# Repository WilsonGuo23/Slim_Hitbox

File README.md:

# Slim Hitbox Enclosure

This repository contains 3D models, assembly instructions, and detailed documentation for building a compact, 3D-printed hitbox-style arcade controller.

## Project Overview

This Slim Hitbox Enclosure provides a slim, portable alternative to traditional arcade controllers, making it ideal for travel and easy setup. It supports 3D printing, simple assembly, and an ergonomic design. 

> **Note**: Version 1 is exclusively in the southpaw (left-handed) layout. Currently, there is no orthodox (right-handed) version.

## Features

- **Compact and Slim Design**: A low-profile layout optimized for easy handling and storage.
- **3D Printable Components**: Fully printable in standard PLA/ABS materials.
- **Ergonomic Design**: Includes a wrist rest for comfort.
- **Comfortable Assembly**: Chamfered screw holes provide a smoother finish.

## Attributions

This project uses GP2040 to enable the microcontroller to function as a game controller. Special thanks to the knowledgeable members of the GP2040 Discord community for their assistance and expertise, and to the helpful contributors on the r/pcb subreddit for reviewing the board's usability before it was sent for production.

## Prerequisites

- Access to a 3D printer and filament (PLA, ABS, or similar recommended)
- Personal Computer with USB port
- Soldering equipment and basic assembly tools

## Instructions

1. **PCB Manufacturing**: Have the PCB manufactured using the Gerber files in the `fab` folder.
2. **Download STL Files**: Access the STL files from the `models` directory.
3. **Slice and Print**: Use slicing software like Cura or PrusaSlicer to prepare and print the models. Adjust settings as needed based on your specific printer and filament.
4. **Assemble**: Follow the assembly instructions below.

## Parts List

- **Buttons**: 9x 30mm buttons, 3x 24mm buttons
- **Keycaps**: 5x keycaps
- **Panels**: 1x top panel, 1x bottom panel
- **Cables**: 1x Micro USB male to USB male cable ([link](https://www.amazon.com/gp/product/B08BZD66H4/ref=ppx_yo_dt_b_search_asin_title?ie=UTF8&psc=1)) 1x, 1x USB female to USB male cable
  1. (length should match your preferred distance to console or PC)
- **Hardware**: 6x M3 x 20mm screws, 6x M3 bolts
- **Feet**: 6x printed feet
  1. (ensure bolts fit snugly)
- **Electrical Components**:
  - 1x Raspberry Pi Pico
  - 17x MX Cherry or MX Cherry-compatible keyswitches
  - 2 rows of 100-pin male header pins ([link](https://www.amazon.com/dp/B06ZZN8L9S?ref=ppx_yo2ov_dt_b_fed_asin_title))
  - 1x PCB

## Assembly Instructions

1. **Prepare Feet**: Apply a strong bonding agent to the inner walls of each foot, then insert bolts into all six printed feet.
2. **Microcontroller Setup**: Solder male header pins to the Pico microcontroller.
3. **PCB Assembly**: Solder the microcontroller to the PCB using the header pins.
4. **Keyswitch Installation**: Solder all 17 keyswitches onto the PCB.
5. **Cable Guide**: Attach the Micro USB to USB cable to the Pico and guide it through the channels in the top panel.
6. **Enclosure Assembly**: Place the PCB between the top and bottom panels.
7. **Secure Panels**: Screw the panels together and attach them with the feet.
8. **Install Buttons**: Attach all printed buttons, following the image shown below.

9. **Attach USB Cable**: Connect the USB female-to-male cable to the exposed USB head.

## Configuration

1. **Download Firmware**: Get the appropriate microcontroller `.uf2` file from the [GP2040 website](https://gp2040-ce.info/downloads/).
2. **Connect and Install Firmware**: Plug the USB cable into a PC, then drag the `.uf2` file into the storage device that appears in the file explorer when the hitbox is connected.
3. **Configuration Setup**: If the default layout is unsatisfactory, use the [web configurator](https://gp2040-ce.info/web-configurator/) to customize the button layout.
4. **Ready to Play**: Boot up your favorite fighting game and enjoy!

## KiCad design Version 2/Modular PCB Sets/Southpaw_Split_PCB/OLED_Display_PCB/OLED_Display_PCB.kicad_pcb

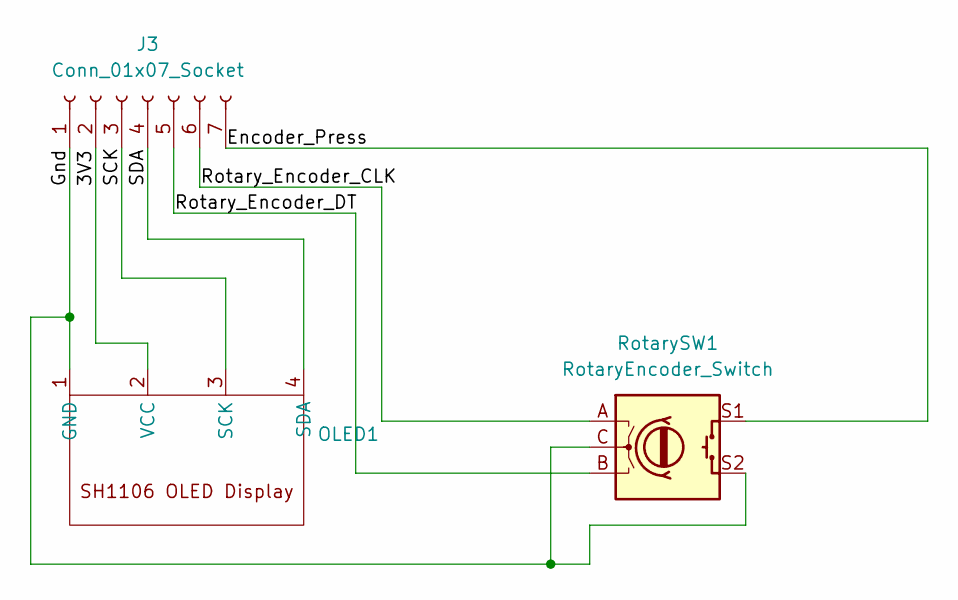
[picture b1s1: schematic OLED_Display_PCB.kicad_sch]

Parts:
J3: Conn_01x07_Socket; JST_PH_B7B-PH-K_1x07_P2.00mm_Vertical
OLED1: Hosyond SH1106 OLED Display
RotarySW1: RotaryEncoder_Switch; RotaryEncoder_Alps_EC11E-Switch_Vertical_H20mm

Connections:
/3V3: J3.2, OLED1.2 (VCC)
/Encoder_Press: J3.7, RotarySW1.S1
/Gnd: J3.1, OLED1.1 (GND), RotarySW1.C, RotarySW1.S2
/Rotary_Encoder_CLK: J3.6, RotarySW1.A
/Rotary_Encoder_DT: J3.5, RotarySW1.B
/SCK: J3.3, OLED1.3 (SCK)
/SDA: J3.4, OLED1.4 (SDA)

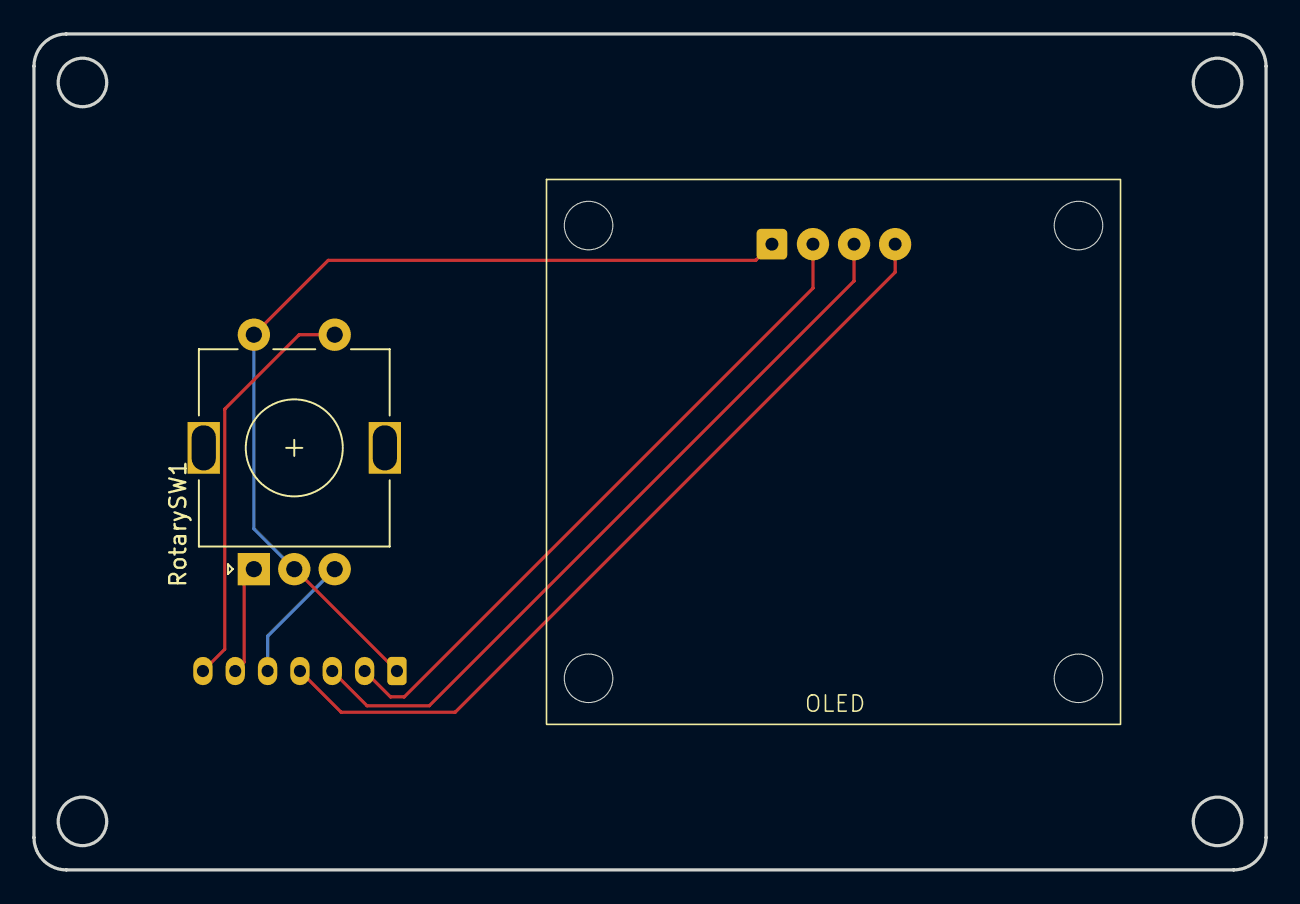
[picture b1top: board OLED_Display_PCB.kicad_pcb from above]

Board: 2 copper layers, 76.2 x 51.7 mm, 3 parts (1 on the bottom side), 7 nets.

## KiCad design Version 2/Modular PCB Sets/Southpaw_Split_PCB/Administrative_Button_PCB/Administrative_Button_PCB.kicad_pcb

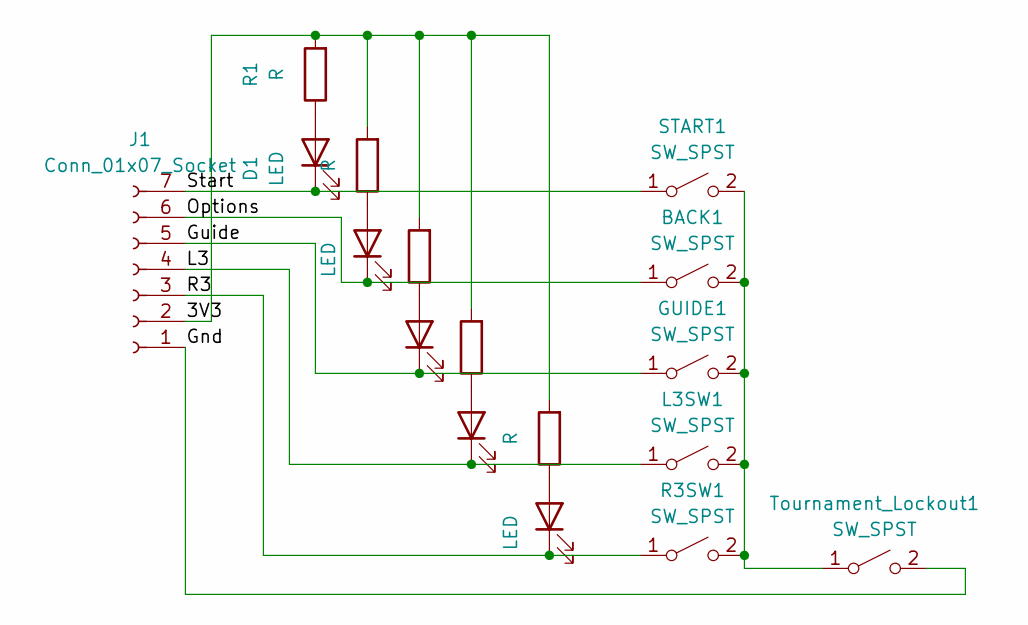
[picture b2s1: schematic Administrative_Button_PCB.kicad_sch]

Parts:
BACK1: SW_SPST; SW_Cherry_MX_1.00u_PCB
D1, D2, D3, D4, D5: LED; LED_D5.0mm
GUIDE1: SW_SPST; SW_Cherry_MX_1.00u_PCB
J1: Conn_01x07_Socket; JST_PH_B7B-PH-K_1x07_P2.00mm_Vertical
L3SW1: SW_SPST; SW_Cherry_MX_1.00u_PCB
R1, R2, R3, R4, R5: R; R_Axial_DIN0207_L6.3mm_D2.5mm_P10.16mm_Horizontal
R3SW1: SW_SPST; SW_Cherry_MX_1.00u_PCB
START1: SW_SPST; SW_Cherry_MX_1.00u_PCB
Tournament_Lockout1: SW_SPST; MTS-101 Toggle Switch

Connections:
/3V3: J1.2, R1.2, R2.2, R3.2, R4.2, R5.2
/Gnd: J1.1, Tournament_Lockout1.2 (B)
/Guide: D3.1 (K), GUIDE1.1 (A), J1.5
/L3: D4.1 (K), J1.4, L3SW1.1 (A)
/Options: BACK1.1 (A), D2.1 (K), J1.6
/R3: D5.1 (K), J1.3, R3SW1.1 (A)
/Start: D1.1 (K), J1.7, START1.1 (A)
unnamed: BACK1.2 (B), GUIDE1.2 (B), L3SW1.2 (B), R3SW1.2 (B), START1.2 (B), Tournament_Lockout1.1 (A)
unnamed: D1.2 (A), R1.1
unnamed: D2.2 (A), R2.1
unnamed: D3.2 (A), R3.1
unnamed: D4.2 (A), R4.1
unnamed: D5.2 (A), R5.1

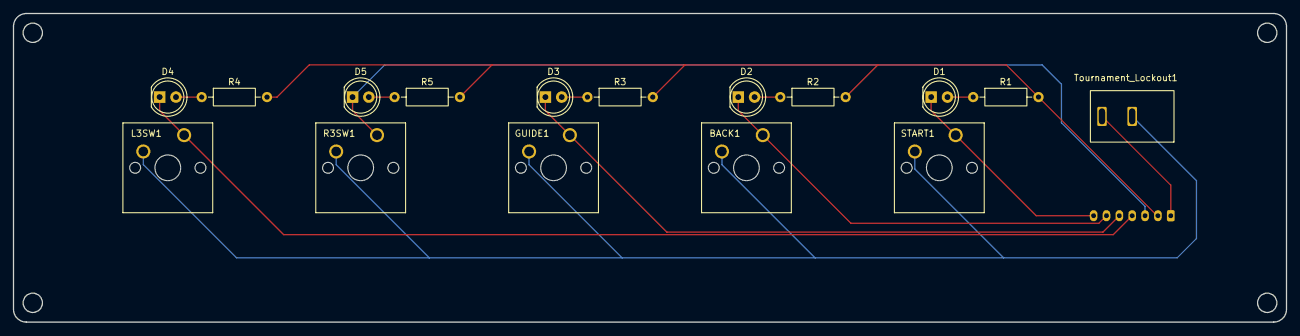
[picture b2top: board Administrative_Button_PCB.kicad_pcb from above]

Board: 2 copper layers, 198.0 x 48.0 mm, 17 parts (1 on the bottom side), 13 nets.

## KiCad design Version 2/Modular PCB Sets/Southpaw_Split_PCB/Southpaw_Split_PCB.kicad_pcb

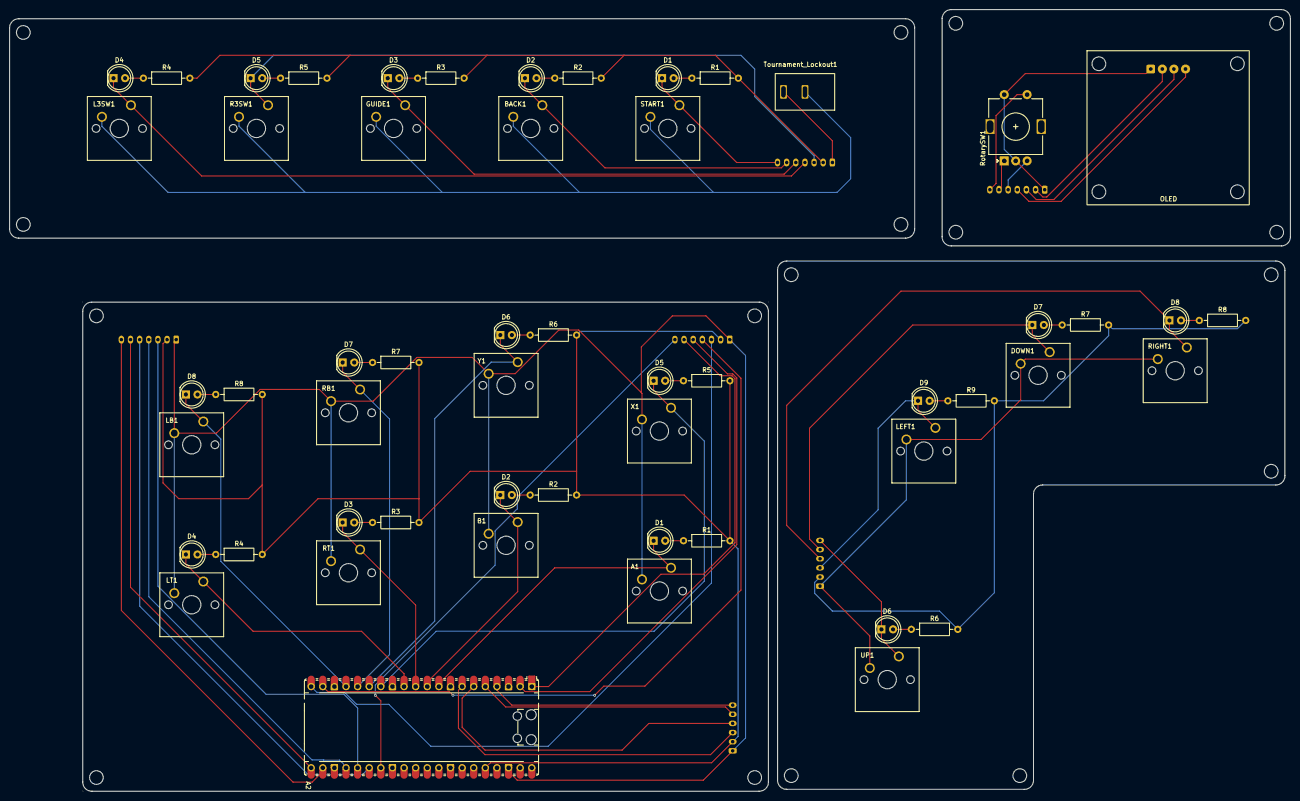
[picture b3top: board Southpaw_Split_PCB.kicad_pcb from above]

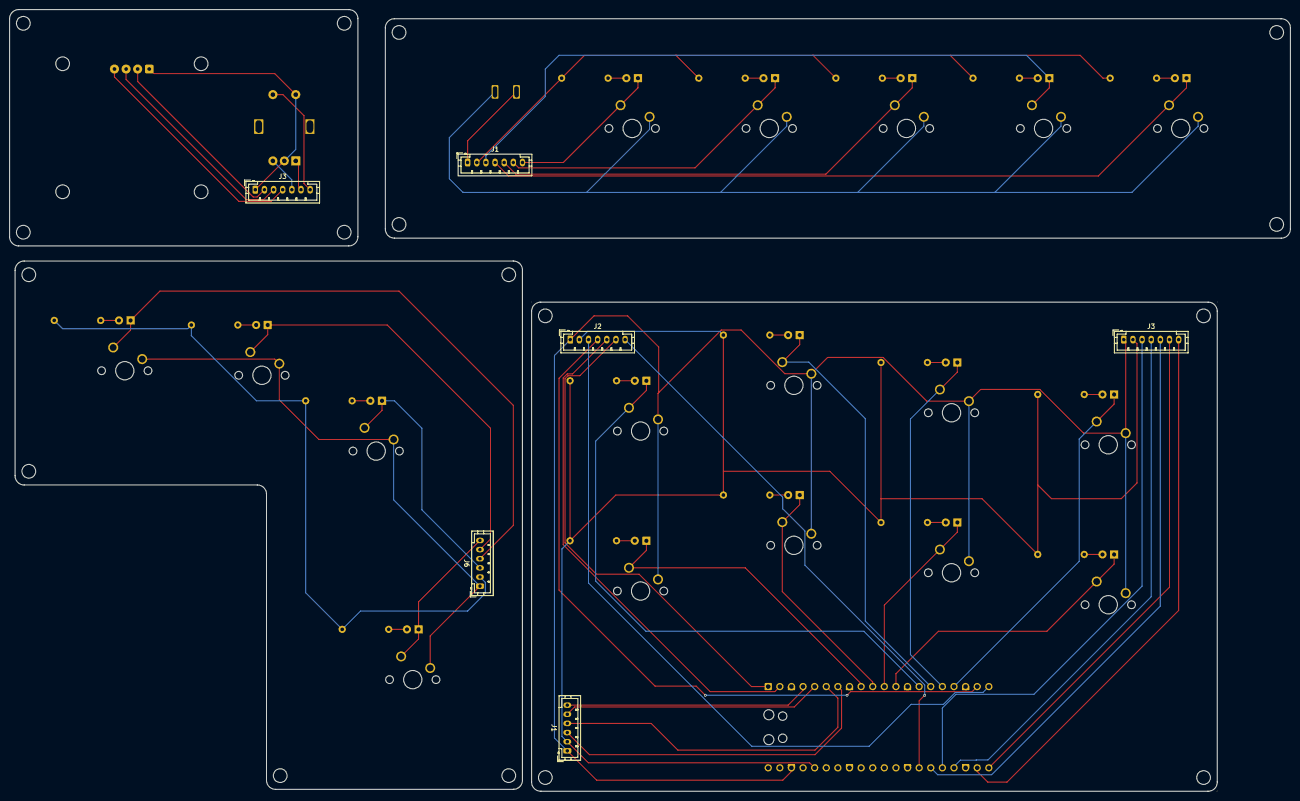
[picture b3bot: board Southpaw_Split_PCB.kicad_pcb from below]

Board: 2 copper layers, 280.2 x 171.0 mm, 61 parts (6 on the bottom side), 37 nets.

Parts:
A1: SW_SPST; SW_Cherry_MX_1.00u_PCB
A2: RaspberryPi_Pico; RaspberryPi_Pico_Common_Unspecified
B1: SW_SPST; SW_Cherry_MX_1.00u_PCB
BACK1: SW_SPST; SW_Cherry_MX_1.00u_PCB
D1, D1#2, D2, D2#2, D3, D3#2, D4, D4#2, D5, D5#2, D6, D6#2, D7, D7#2, D8, D8#2, D9: LED; LED_D5.0mm
DOWN1: SW_SPST; SW_Cherry_MX_1.00u_PCB
GUIDE1: SW_SPST; SW_Cherry_MX_1.00u_PCB
J1, J6: Conn_01x06_Socket; JST_PH_B6B-PH-K_1x06_P2.00mm_Vertical
J1#2, J2, J3, J3#2: Conn_01x07_Socket; JST_PH_B7B-PH-K_1x07_P2.00mm_Vertical
L3SW1: SW_SPST; SW_Cherry_MX_1.00u_PCB
LB1: SW_SPST; SW_Cherry_MX_1.00u_PCB
LEFT1: SW_SPST; SW_Cherry_MX_1.00u_PCB
LT1: SW_SPST; SW_Cherry_MX_1.00u_PCB
OLED1: Hosyond SH1106 OLED Display
R1, R1#2, R2, R2#2, R3, R3#2, R4, R4#2, R5, R5#2, R6, R6#2, R7, R7#2, R8, R8#2, R9: R; R_Axial_DIN0207_L6.3mm_D2.5mm_P10.16mm_Horizontal
R3SW1: SW_SPST; SW_Cherry_MX_1.00u_PCB
RB1: SW_SPST; SW_Cherry_MX_1.00u_PCB
RIGHT1: SW_SPST; SW_Cherry_MX_1.00u_PCB
RT1: SW_SPST; SW_Cherry_MX_1.00u_PCB
RotarySW1: RotaryEncoder_Switch; RotaryEncoder_Alps_EC11E-Switch_Vertical_H20mm
START1: SW_SPST; SW_Cherry_MX_1.00u_PCB
Tournament_Lockout1: SW_SPST; MTS-101 Toggle Switch
UP1: SW_SPST; SW_Cherry_MX_1.00u_PCB
X1: SW_SPST; SW_Cherry_MX_1.00u_PCB
Y1: SW_SPST; SW_Cherry_MX_1.00u_PCB

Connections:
3v3: A2.36 (3V3), J1.2, J2.2, J3#2.2, R1.2, R2#2.2, R3#2.2, R4.2, R5.2, R6#2.2, R7.2, R8.2
/3V3: J1#2.2, J3.2, OLED1.2 (VCC), R1#2.2, R2.2, R3.2, R4#2.2, R5#2.2
/3v3: J6.2, R6.2, R7#2.2, R8#2.2, R9.2
/Down: A2.5 (GPIO3), D7.1 (K), DOWN1.1 (A), J1.5, J6.5
/Encoder_Press: A2.27 (GPIO21), J2.7, J3.7, RotarySW1.S1
/Gnd: DOWN1.2 (B), J1#2.1, J3.1, J6.1, LEFT1.2 (B), OLED1.1 (GND), RIGHT1.2 (B), RotarySW1.C, RotarySW1.S2, Tournament_Lockout1.2 (B), UP1.2 (B)
/Guide: A2.26 (GPIO20), D3#2.1 (K), GUIDE1.1 (A), J1#2.5, J3#2.5
/L3: A2.24 (GPIO18), D4#2.1 (K), J1#2.4, J3#2.4, L3SW1.1 (A)
/Left: A2.7 (GPIO5), D9.1 (K), J1.3, J6.3, LEFT1.1 (A)
/Options: A2.21 (GPIO16), BACK1.1 (A), D2#2.1 (K), J1#2.6, J3#2.6
/R3: A2.25 (GPIO19), D5#2.1 (K), J1#2.3, J3#2.3, R3SW1.1 (A)
/Right: A2.6 (GPIO4), D8.1 (K), J1.4, J6.4, RIGHT1.1 (A)
/Rotary_Encoder_CLK: A2.1 (GPIO0), J2.6, J3.6, RotarySW1.A
/Rotary_Encoder_DT: A2.2 (GPIO1), J2.5, J3.5, RotarySW1.B
/SCK: A2.20 (GPIO15), J2.3, J3.3, OLED1.3 (SCK)
/SDA: A2.19 (GPIO14), J2.4, J3.4, OLED1.4 (SDA)
/Start: A2.22 (GPIO17), D1.1 (K), J1#2.7, J3#2.7, START1.1 (A)
/Up: A2.4 (GPIO2), D6.1 (K), J1.6, J6.6, UP1.1 (A)
A: A1.1 (A), A2.9 (GPIO6), D1#2.1 (K)
B: A2.10 (GPIO7), B1.1 (A), D2.1 (K)
GND: A1.2 (B), A2.3 (GND), A2.8 (GND), A2.13 (GND), A2.18 (GND), A2.23 (GND), A2.28 (GND), A2.38 (GND), B1.2 (B), J1.1, J2.1, J3#2.1, LB1.2 (B), LT1.2 (B), RB1.2 (B), RT1.2 (B), X1.2 (B), Y1.2 (B)
LB: A2.17 (GPIO13), D8#2.1 (K), LB1.1 (A)
LT: A2.12 (GPIO9), D4.1 (K), LT1.1 (A)
unnamed: BACK1.2 (B), GUIDE1.2 (B), L3SW1.2 (B), R3SW1.2 (B), START1.2 (B), Tournament_Lockout1.1 (A)
unnamed: D1.2 (A), D1#2.2 (A), R1.1, R1#2.1
unnamed: D2.2 (A), D2#2.2 (A), R2.1, R2#2.1
unnamed: D3.2 (A), D3#2.2 (A), R3.1, R3#2.1
unnamed: D4.2 (A), D4#2.2 (A), R4.1, R4#2.1
unnamed: D5.2 (A), D5#2.2 (A), R5.1, R5#2.1
unnamed: D6.2 (A), D6#2.2 (A), R6.1, R6#2.1
unnamed: D7.2 (A), D7#2.2 (A), R7.1, R7#2.1
unnamed: D8.2 (A), D8#2.2 (A), R8.1, R8#2.1
unnamed: D9.2 (A), R9.1
RB: A2.16 (GPIO12), D7#2.1 (K), RB1.1 (A)
RT: A2.11 (GPIO8), D3.1 (K), RT1.1 (A)
X: A2.14 (GPIO10), D5.1 (K), X1.1 (A)
Y: A2.15 (GPIO11), D6#2.1 (K), Y1.1 (A)

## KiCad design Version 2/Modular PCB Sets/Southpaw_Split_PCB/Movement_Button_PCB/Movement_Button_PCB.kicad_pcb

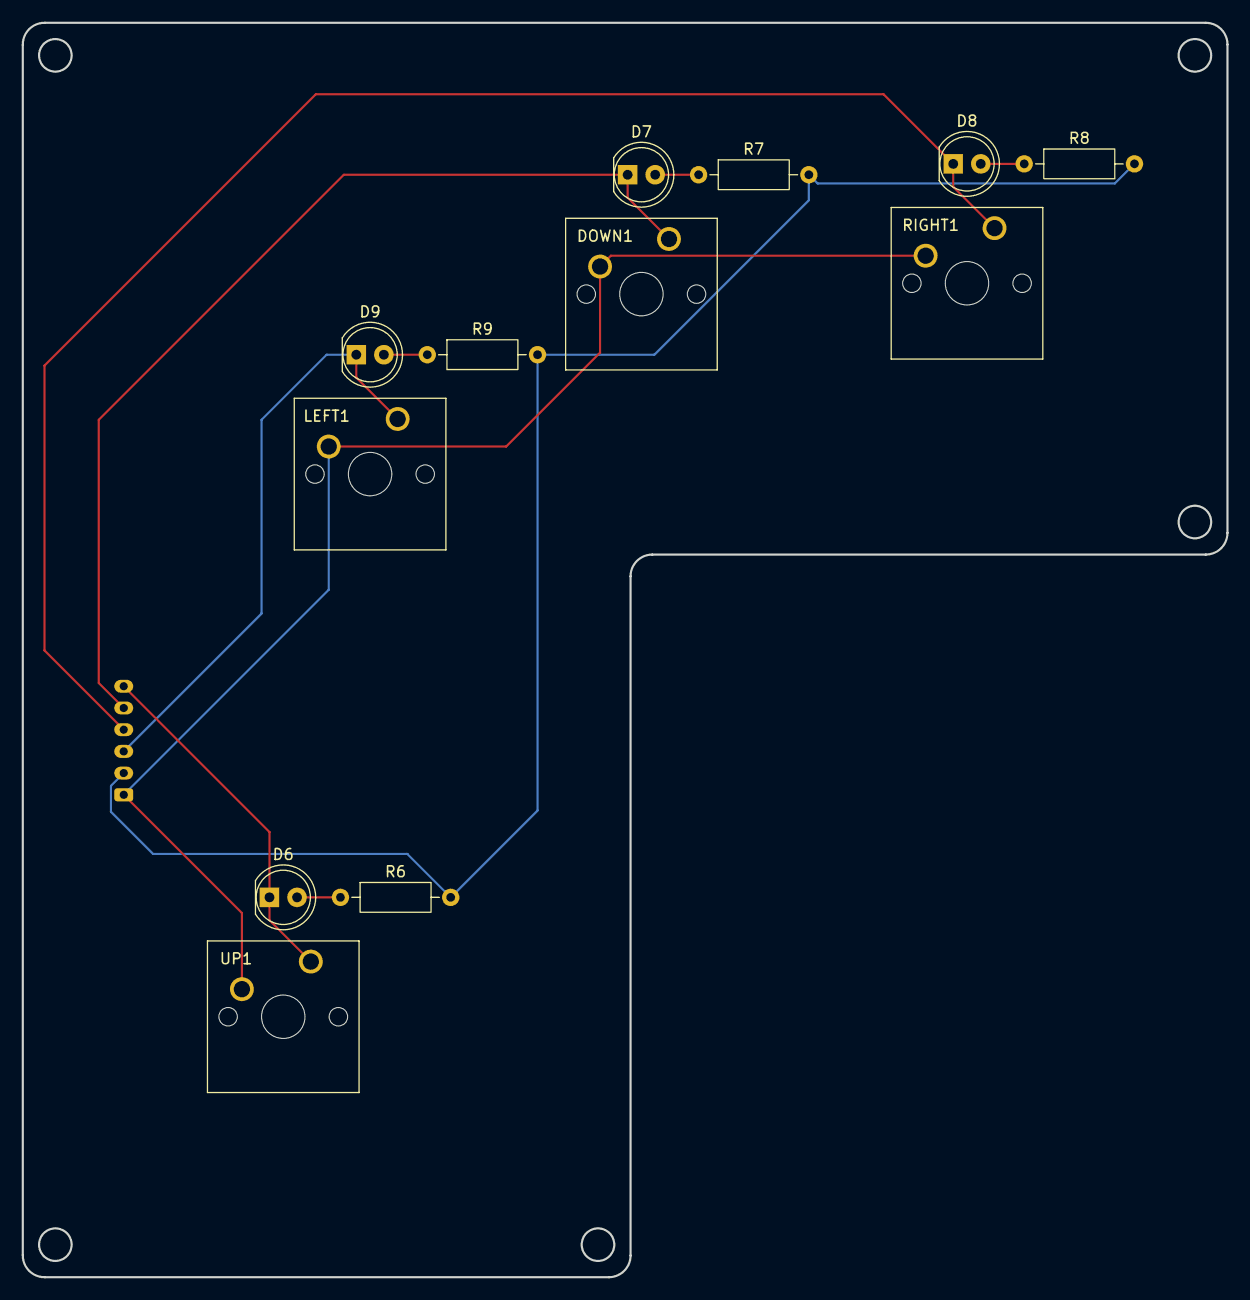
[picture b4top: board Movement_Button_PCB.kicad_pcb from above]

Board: 2 copper layers, 111.0 x 115.6 mm, 13 parts (1 on the bottom side), 10 nets.

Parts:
D6, D7, D8, D9: LED; LED_D5.0mm
DOWN1: SW_SPST; SW_Cherry_MX_1.00u_PCB
J6: Conn_01x06_Socket; JST_PH_B6B-PH-K_1x06_P2.00mm_Vertical
LEFT1: SW_SPST; SW_Cherry_MX_1.00u_PCB
R6, R7, R8, R9: R; R_Axial_DIN0207_L6.3mm_D2.5mm_P10.16mm_Horizontal
RIGHT1: SW_SPST; SW_Cherry_MX_1.00u_PCB
UP1: SW_SPST; SW_Cherry_MX_1.00u_PCB

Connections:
/3v3: J6.2, R6.2, R7.2, R8.2, R9.2
/Down: D7.1 (K), DOWN1.1 (A), J6.5
/Gnd: DOWN1.2 (B), J6.1, LEFT1.2 (B), RIGHT1.2 (B), UP1.2 (B)
/Left: D9.1 (K), J6.3, LEFT1.1 (A)
/Right: D8.1 (K), J6.4, RIGHT1.1 (A)
/Up: D6.1 (K), J6.6, UP1.1 (A)
unnamed: D6.2 (A), R6.1
unnamed: D7.2 (A), R7.1
unnamed: D8.2 (A), R8.1
unnamed: D9.2 (A), R9.1

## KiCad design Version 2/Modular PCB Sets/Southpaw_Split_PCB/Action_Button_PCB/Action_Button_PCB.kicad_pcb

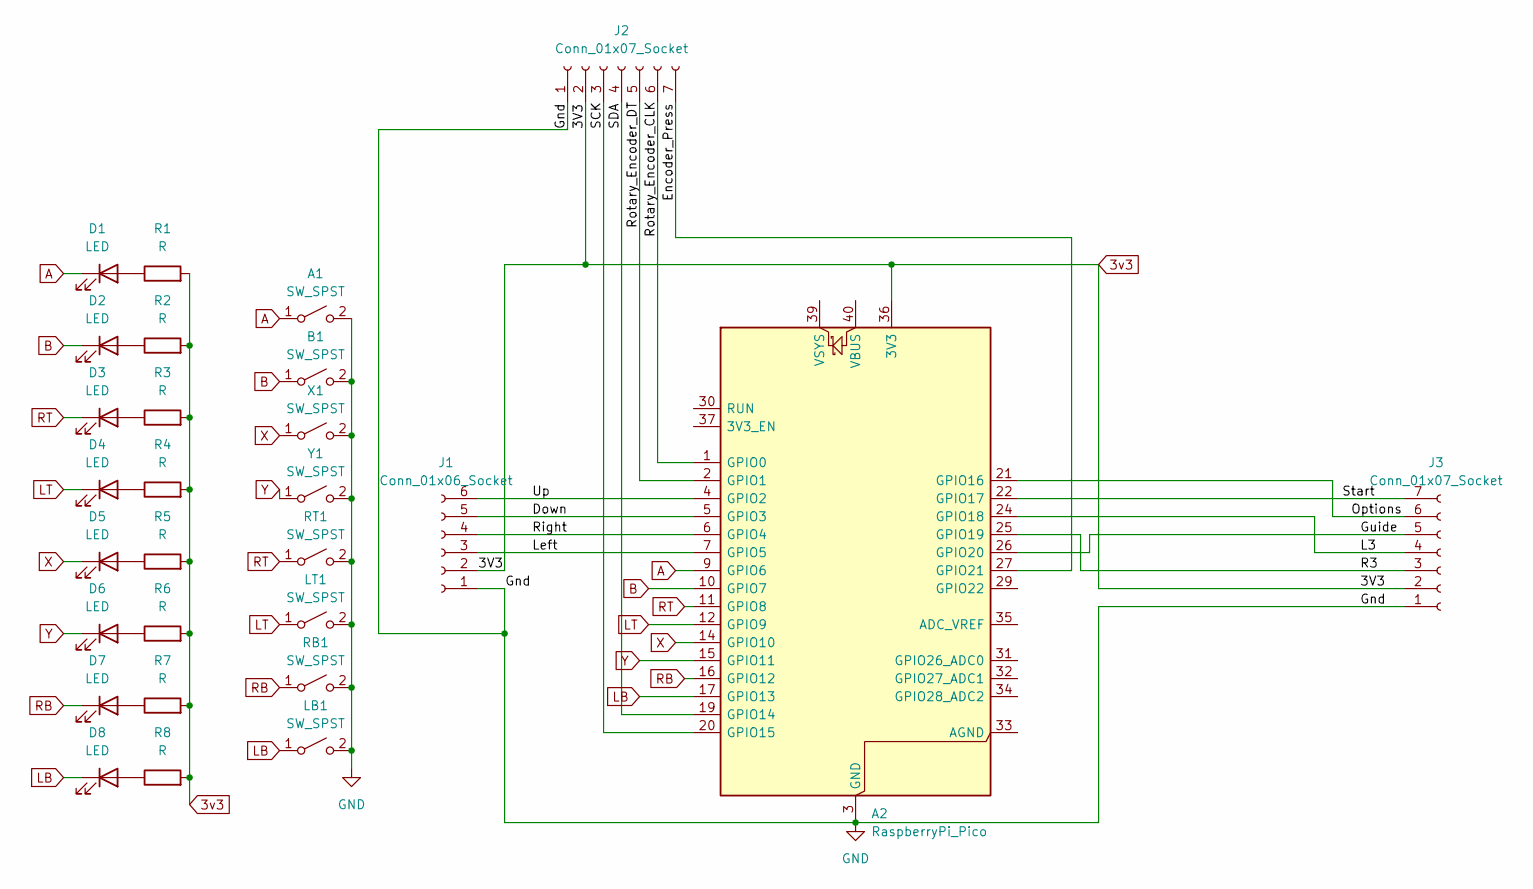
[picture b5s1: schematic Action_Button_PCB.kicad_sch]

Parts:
A1: SW_SPST; SW_Cherry_MX_1.00u_PCB
A2: RaspberryPi_Pico; RaspberryPi_Pico_Common_Unspecified
B1: SW_SPST; SW_Cherry_MX_1.00u_PCB
D1, D2, D3, D4, D5, D6, D7, D8: LED; LED_D5.0mm
J1: Conn_01x06_Socket; JST_PH_B6B-PH-K_1x06_P2.00mm_Vertical
J2, J3: Conn_01x07_Socket; JST_PH_B7B-PH-K_1x07_P2.00mm_Vertical
LB1: SW_SPST; SW_Cherry_MX_1.00u_PCB
LT1: SW_SPST; SW_Cherry_MX_1.00u_PCB
R1, R2, R3, R4, R5, R6, R7, R8: R; R_Axial_DIN0207_L6.3mm_D2.5mm_P10.16mm_Horizontal
RB1: SW_SPST; SW_Cherry_MX_1.00u_PCB
RT1: SW_SPST; SW_Cherry_MX_1.00u_PCB
X1: SW_SPST; SW_Cherry_MX_1.00u_PCB
Y1: SW_SPST; SW_Cherry_MX_1.00u_PCB

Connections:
3v3: A2.36 (3V3), J1.2, J2.2, J3.2, R1.2, R2.2, R3.2, R4.2, R5.2, R6.2, R7.2, R8.2
/Down: A2.5 (GPIO3), J1.5
/Encoder_Press: A2.27 (GPIO21), J2.7
/Guide: A2.26 (GPIO20), J3.5
/L3: A2.24 (GPIO18), J3.4
/Left: A2.7 (GPIO5), J1.3
/Options: A2.21 (GPIO16), J3.6
/R3: A2.25 (GPIO19), J3.3
/Right: A2.6 (GPIO4), J1.4
/Rotary_Encoder_CLK: A2.1 (GPIO0), J2.6
/Rotary_Encoder_DT: A2.2 (GPIO1), J2.5
/SCK: A2.20 (GPIO15), J2.3
/SDA: A2.19 (GPIO14), J2.4
/Start: A2.22 (GPIO17), J3.7
/Up: A2.4 (GPIO2), J1.6
A: A1.1 (A), A2.9 (GPIO6), D1.1 (K)
B: A2.10 (GPIO7), B1.1 (A), D2.1 (K)
GND: A1.2 (B), A2.3 (GND), A2.8 (GND), A2.13 (GND), A2.18 (GND), A2.23 (GND), A2.28 (GND), A2.38 (GND), B1.2 (B), J1.1, J2.1, J3.1, LB1.2 (B), LT1.2 (B), RB1.2 (B), RT1.2 (B), X1.2 (B), Y1.2 (B)
LB: A2.17 (GPIO13), D8.1 (K), LB1.1 (A)
LT: A2.12 (GPIO9), D4.1 (K), LT1.1 (A)
unnamed: D1.2 (A), R1.1
unnamed: D2.2 (A), R2.1
unnamed: D3.2 (A), R3.1
unnamed: D4.2 (A), R4.1
unnamed: D5.2 (A), R5.1
unnamed: D6.2 (A), R6.1
unnamed: D7.2 (A), R7.1
unnamed: D8.2 (A), R8.1
RB: A2.16 (GPIO12), D7.1 (K), RB1.1 (A)
RT: A2.11 (GPIO8), D3.1 (K), RT1.1 (A)
X: A2.14 (GPIO10), D5.1 (K), X1.1 (A)
Y: A2.15 (GPIO11), D6.1 (K), Y1.1 (A)

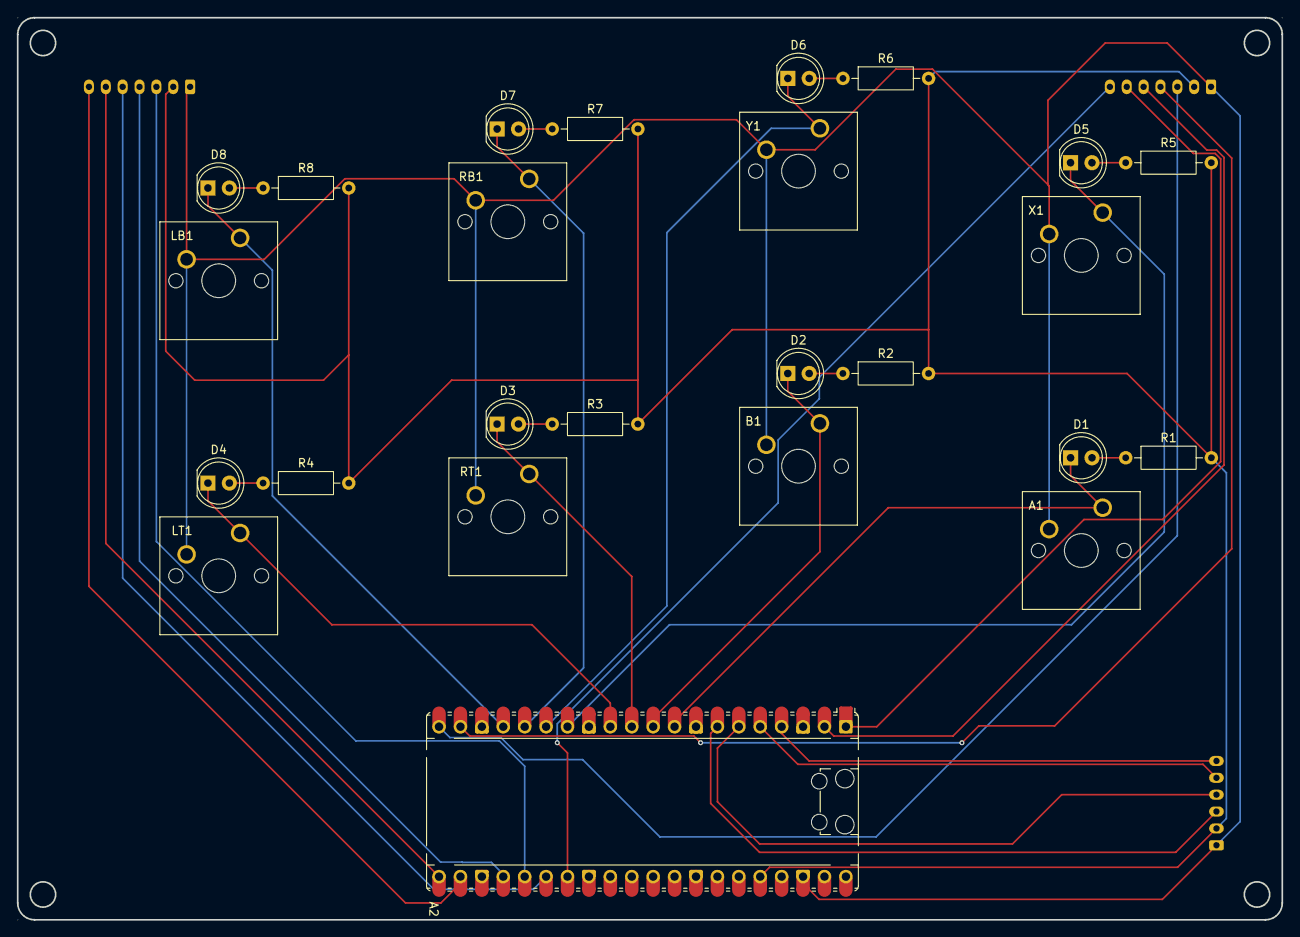
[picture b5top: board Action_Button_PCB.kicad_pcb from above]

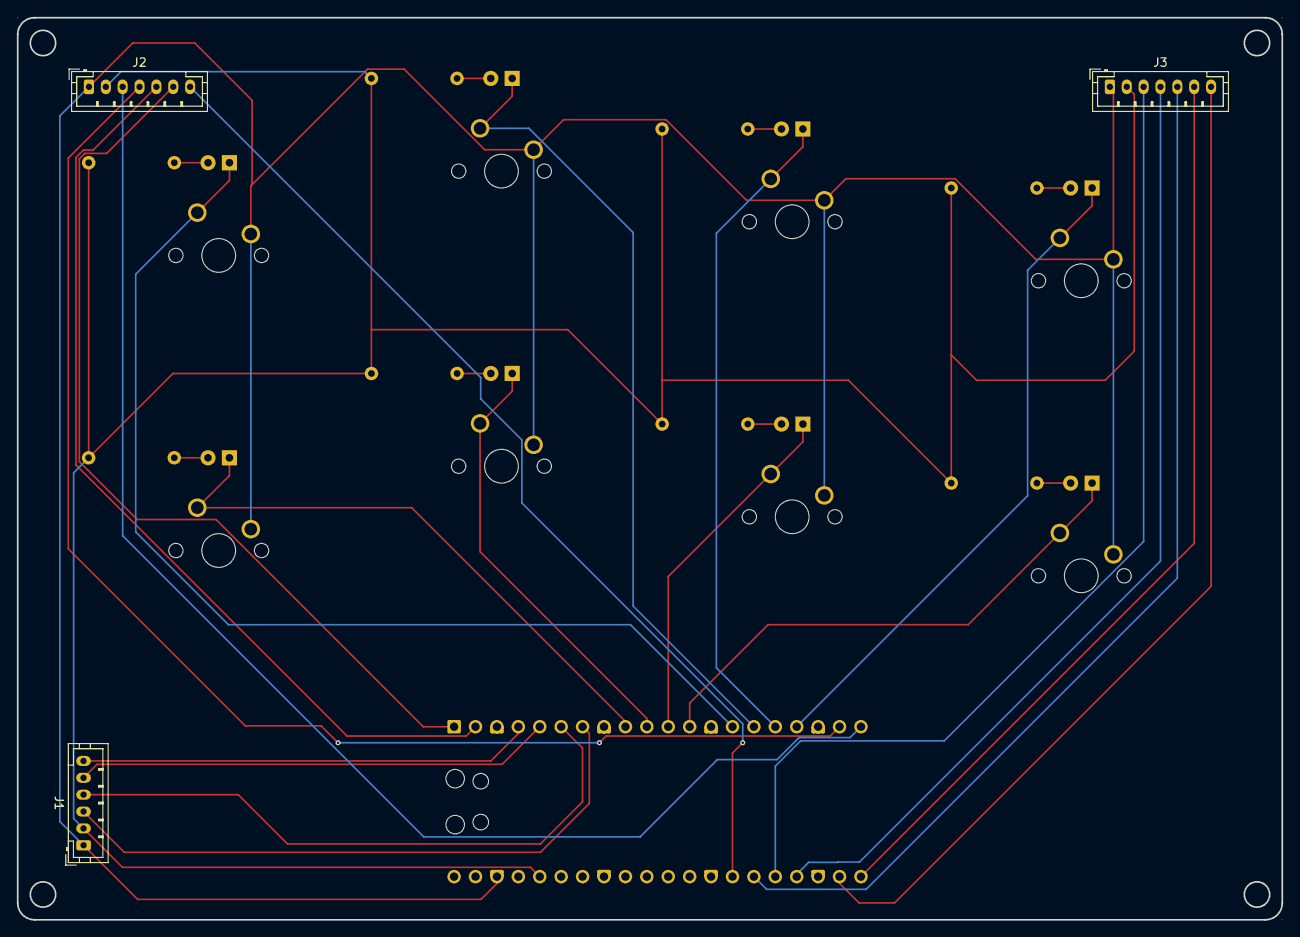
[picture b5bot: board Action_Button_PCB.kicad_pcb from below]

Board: 2 copper layers, 150.0 x 107.0 mm, 28 parts (3 on the bottom side), 32 nets.

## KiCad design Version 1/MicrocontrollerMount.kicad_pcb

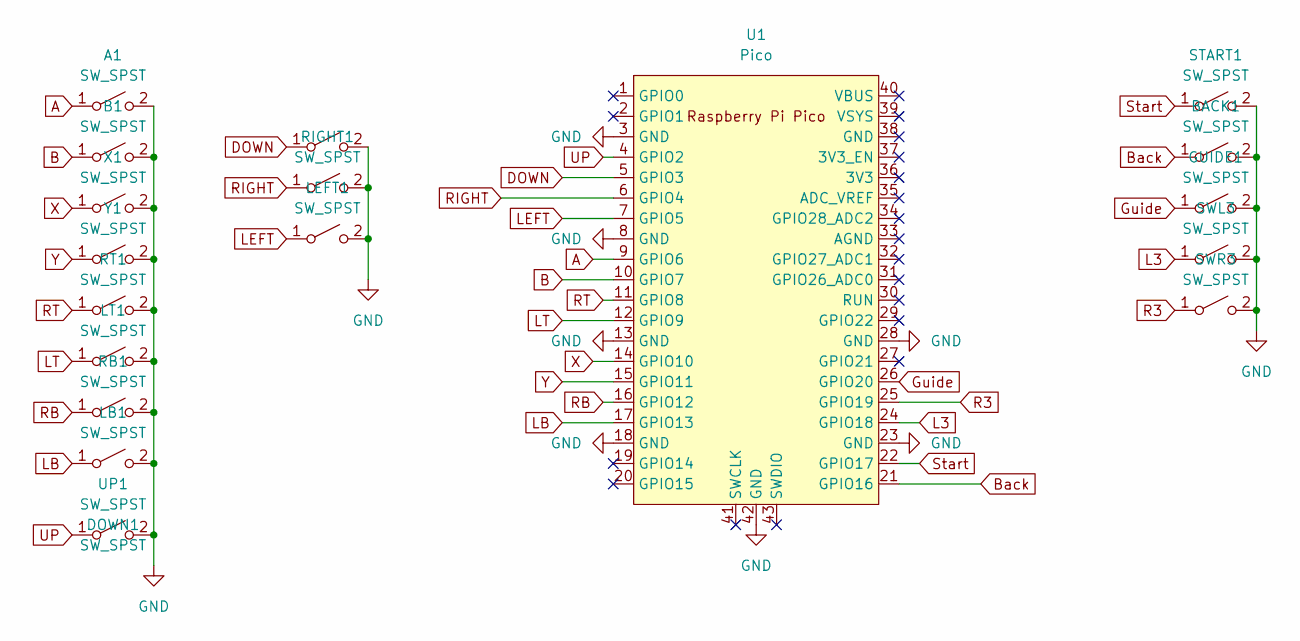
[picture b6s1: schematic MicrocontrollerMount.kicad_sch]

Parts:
A1: SW_SPST; SW_Cherry_MX_1.00u_PCB
B1: SW_SPST; SW_Cherry_MX_1.00u_PCB
BACK1: SW_SPST; SW_Cherry_MX_1.00u_PCB
DOWN1: SW_SPST; SW_Cherry_MX_1.00u_PCB
GUIDE1: SW_SPST; SW_Cherry_MX_1.00u_PCB
LB1: SW_SPST; SW_Cherry_MX_1.00u_PCB
LEFT1: SW_SPST; SW_Cherry_MX_1.00u_PCB
LT1: SW_SPST; SW_Cherry_MX_1.00u_PCB
RB1: SW_SPST; SW_Cherry_MX_1.00u_PCB
RIGHT1: SW_SPST; SW_Cherry_MX_1.00u_PCB
RT1: SW_SPST; SW_Cherry_MX_1.00u_PCB
START1: SW_SPST; SW_Cherry_MX_1.00u_PCB
SWL3: SW_SPST; SW_Cherry_MX_1.00u_PCB
SWR3: SW_SPST; SW_Cherry_MX_1.00u_PCB
U1: Pico; RPi_Pico_SMD_TH
UP1: SW_SPST; SW_Cherry_MX_1.00u_PCB
X1: SW_SPST; SW_Cherry_MX_1.00u_PCB
Y1: SW_SPST; SW_Cherry_MX_1.00u_PCB

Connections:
A: A1.1 (A), U1.9 (GPIO6)
B: B1.1 (A), U1.10 (GPIO7)
Back: BACK1.1 (A), U1.21 (GPIO16)
DOWN: DOWN1.1 (A), U1.5 (GPIO3)
GND: A1.2 (B), B1.2 (B), BACK1.2 (B), DOWN1.2 (B), GUIDE1.2 (B), LB1.2 (B), LEFT1.2 (B), LT1.2 (B), RB1.2 (B), RIGHT1.2 (B), RT1.2 (B), START1.2 (B), SWL3.2 (B), SWR3.2 (B), U1.3 (GND), U1.8 (GND), U1.13 (GND), U1.18 (GND), U1.23 (GND), U1.28 (GND), U1.42 (GND), UP1.2 (B), X1.2 (B), Y1.2 (B)
Guide: GUIDE1.1 (A), U1.26 (GPIO20)
L3: SWL3.1 (A), U1.24 (GPIO18)
LB: LB1.1 (A), U1.17 (GPIO13)
LEFT: LEFT1.1 (A), U1.7 (GPIO5)
LT: LT1.1 (A), U1.12 (GPIO9)
R3: SWR3.1 (A), U1.25 (GPIO19)
RB: RB1.1 (A), U1.16 (GPIO12)
RIGHT: RIGHT1.1 (A), U1.6 (GPIO4)
RT: RT1.1 (A), U1.11 (GPIO8)
Start: START1.1 (A), U1.22 (GPIO17)
UP: U1.4 (GPIO2), UP1.1 (A)
X: U1.14 (GPIO10), X1.1 (A)
Y: U1.15 (GPIO11), Y1.1 (A)

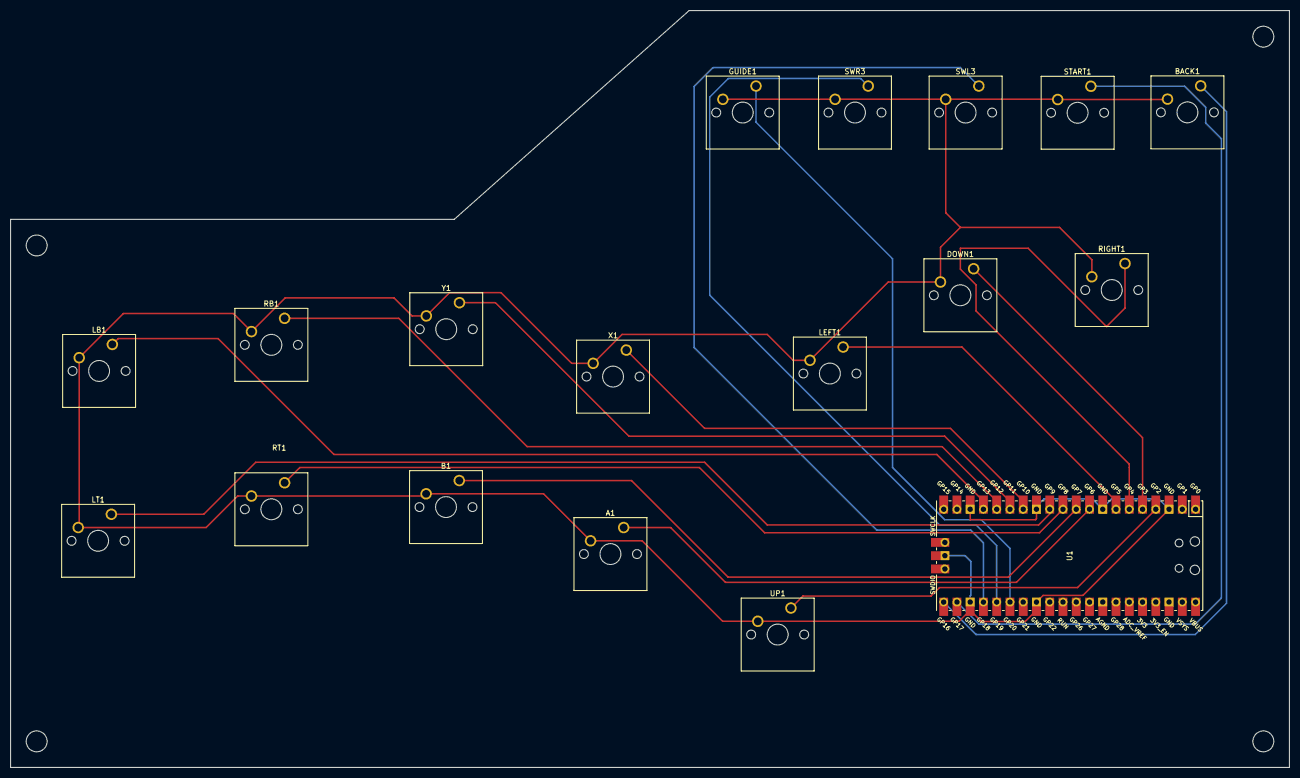
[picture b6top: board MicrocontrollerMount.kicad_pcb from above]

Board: 2 copper layers, 245.0 x 145.0 mm, 18 parts (0 on the bottom side), 18 nets.

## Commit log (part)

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2026-03-06 Refine README introduction for clarity
    Removed redundant welcome message from README.
